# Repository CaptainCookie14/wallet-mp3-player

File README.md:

# wallet-mp3-player
This project is a small, portable MP3 player, designed to be roughly the size of a credit card. This project is all about minimal power consumption, small PCB design, and ease of use for the player.

HOW TO USE IT Insert a micro SD card containing MP3 or WAV files into the device. Turn it on using the battery and play the songs using the buttons. It does not require a phone or computer to play songs. Users can play, pause, and skip songs, and also change the volume using the buttons.

Features

Plays MP3 audio files Ultra-compact PCB design (credit card sized) Button-based controls (play/pause, next, previous, volume) Supports microSD storage for music files Low power consumption for portable devices Optional output for headphones or small speakers

HOW IT WORKS:

It is composed of a microcontroller, which reads the audio files from a storage module, usually a microSD card. The microcontroller then sends the decoded audio to an amplifier for output.

The buttons are always being read by the microcontroller, which controls the state of the player, the songs being played, and the volume.

HARDWARE USED:

-Microcontroller ( STM32F411CEU6x )
- Micro SD card module
- Audio DAC module
- Small audio amplifier
- Tactile and low-profile buttons
- Lithium battery and charging circuit
- PCB designed in KiCad

WIRING/CONNECTIONS:

- Micro SD card module is connected through SPI
- Audio module is connected through I2S or analog pins
- Buttons are connected to digital GPIOs with pull-ups
- Battery is connected through power management circuit

The goal of this project is to create a fully functional, pocket-sized music player that is:

- as thin as possible (under 5mm)
- at least 5 hours of playing time
- able to fit in your wallet
- cheap as possible to make (under 80$ per unit after considering battery, case, shipping & PCB assembly)

The PCB files in this repository were prepared using the JLCPCB KiCad plugin to streamline manufacturing and assembly.

After completing the schematic and PCB layout in KiCad, the plugin was used to:

Generate production-ready Gerber files
Export drill files (Excellon format)
Create a complete BOM (Bill of Materials) with part numbers
Generate a CPL (Pick and Place file) for SMT assembly
Automatically align component footprints with JLCPCB’s supported parts library

i also added the project files and schematic files used for kiCad

Status

Currently in development / testing stage. PCB revisions and firmware improvements are ongoing and am trying to get my first prototype tested.

BOM MATERIALS LIST:
| Ref                                   | Qty | Value             | Footprint       | LCSC Link                                                                                                                                                                                                                            |
| ------------------------------------- | --- | ----------------- | --------------- | ------------------------------------------------------------------------------------------------------------------------------------------------------------------------------------------------------------------------------------ |
| Y1                                    | 1   | 16 MHz crystal    | 3225            | [https://www.lcsc.com/product-detail/Crystals_YXC-Crystal-CX3225SB16000D0FLJCC_C13738.html](https://www.lcsc.com/product-detail/Crystals_YXC-Crystal-CX3225SB16000D0FLJCC_C13738.html)                                               |
| U5                                    | 1   | TPA6132A2RTE      | WQFN-16         | [https://www.lcsc.com/product-detail/Audio-ICs_Texas-Instruments-TPA6132A2RTE_C2863070.html](https://www.lcsc.com/product-detail/Audio-ICs_Texas-Instruments-TPA6132A2RTE_C2863070.html)                                             |
| U4                                    | 1   | PCM5102A          | TSSOP-20        | [https://www.lcsc.com/product-detail/Audio-ICs_Texas-Instruments-PCM5102A_C1520792.html](https://www.lcsc.com/product-detail/Audio-ICs_Texas-Instruments-PCM5102A_C1520792.html)                                                     |
| U3                                    | 1   | USBLC6-2SC6       | SOT-23-6        | [https://www.lcsc.com/product-detail/TVS-Diodes_STMicroelectronics-USBLC6-2SC6_C7519.html](https://www.lcsc.com/product-detail/TVS-Diodes_STMicroelectronics-USBLC6-2SC6_C7519.html)                                                 |
| U2                                    | 1   | AMS1117           | SOT-223         | [https://www.lcsc.com/product-detail/Linear-Voltage-Regulators_Advanced-Monolithic-Systems-AMS1117-3-3_C6186.html](https://www.lcsc.com/product-detail/Linear-Voltage-Regulators_Advanced-Monolithic-Systems-AMS1117-3-3_C6186.html) |
| U1                                    | 1   | STM32F411CEUx     | QFN-48          | [https://www.lcsc.com/product-detail/Microcontrollers-MCU-ST-Microelectronics-STM32F411CEUx_C60420.html](https://www.lcsc.com/product-detail/Microcontrollers-MCU-ST-Microelectronics-STM32F411CEUx_C60420.html)                     |
| SW2–SW6                               | 5   | Tactile switch    | SMD push button | [https://www.lcsc.com/product-detail/Tactile-Switches_XKB-TS-1187A_C318884.html](https://www.lcsc.com/product-detail/Tactile-Switches_XKB-TS-1187A_C318884.html)                                                                     |
| SW1                                   | 1   | SPDT switch       | PCM12           | [https://www.lcsc.com/product-detail/Slide-Switches_CW-PCM12_C109335.html](https://www.lcsc.com/product-detail/Slide-Switches_CW-PCM12_C109335.html)                                                                                 |
| R15,R16                               | 2   | 5.1kΩ             | 0402            | [https://www.lcsc.com/product-detail/Chip-Resistor-Surface-Mount_YAGEO-RC0402FR-075K1L_C25905.html](https://www.lcsc.com/product-detail/Chip-Resistor-Surface-Mount_YAGEO-RC0402FR-075K1L_C25905.html)                               |
| R13,R14                               | 2   | 10Ω               | 0402            | [https://www.lcsc.com/product-detail/Chip-Resistor-Surface-Mount_YAGEO-RC0402FR-0710RL_C25077.html](https://www.lcsc.com/product-detail/Chip-Resistor-Surface-Mount_YAGEO-RC0402FR-0710RL_C25077.html)                               |
| R11,R12                               | 2   | 450Ω              | 0402            | [https://www.lcsc.com/product-detail/Chip-Resistor-Surface-Mount_YAGEO-RC0402FR-07450RL_C25117.html](https://www.lcsc.com/product-detail/Chip-Resistor-Surface-Mount_YAGEO-RC0402FR-07450RL_C25117.html)                             |
| R2,R3                                 | 2   | 1.5kΩ             | 0402            | [https://www.lcsc.com/product-detail/Chip-Resistor-Surface-Mount_YAGEO-RC0402FR-071K5L_C25867.html](https://www.lcsc.com/product-detail/Chip-Resistor-Surface-Mount_YAGEO-RC0402FR-071K5L_C25867.html)                               |
| R1,R4–R7,R9,R10                       | 7   | 10kΩ              | 0402            | [https://www.lcsc.com/product-detail/Chip-Resistor-Surface-Mount_YAGEO-RC0402FR-0710KL_C25744.html](https://www.lcsc.com/product-detail/Chip-Resistor-Surface-Mount_YAGEO-RC0402FR-0710KL_C25744.html)                               |
| J5                                    | 1   | 3.5mm audio jack  | SMT             | [https://www.lcsc.com/product-detail/Audio-Connectors_CUI-Devices-SJ-3523-SMT_C4991872.html](https://www.lcsc.com/product-detail/Audio-Connectors_CUI-Devices-SJ-3523-SMT_C4991872.html)                                             |
| J4                                    | 1   | USB-C receptacle  | 16P USB2.0      | [https://www.lcsc.com/product-detail/USB-Connectors_XKB-Connectivity-U262-16XN-4BVC11_C2894897.html](https://www.lcsc.com/product-detail/USB-Connectors_XKB-Connectivity-U262-16XN-4BVC11_C2894897.html)                             |
| J2                                    | 1   | Micro SD socket   | TF-01A          | [https://www.lcsc.com/product-detail/Memory-Card-Sockets_Jinling-Group-TF-01A_C91145.html](https://www.lcsc.com/product-detail/Memory-Card-Sockets_Jinling-Group-TF-01A_C91145.html)                                                 |
| J1                                    | 1   | 4-pin header      | 2.54mm          | [https://www.lcsc.com/product-detail/Pin-Header-Sockets_Generic-2-54mm-pin-header_CNA.html](https://www.lcsc.com/product-detail/Pin-Header-Sockets_Generic-2-54mm-pin-header_CNA.html)                                               |
| FB1                                   | 1   | 120Ω ferrite bead | 0603            | [https://www.lcsc.com/product-detail/Ferrite-Beads_Murata-BLM18AG121SN1D_C76892.html](https://www.lcsc.com/product-detail/Ferrite-Beads_Murata-BLM18AG121SN1D_C76892.html)                                                           |
| D1,D2                                 | 2   | LED               | 0805            | [https://www.lcsc.com/product-detail/LED-Indication_YONGYUTAI-0805-LED_C2290.html](https://www.lcsc.com/product-detail/LED-Indication_YONGYUTAI-0805-LED_C2290.html)                                                                 |
| C44,C45                               | 2   | 2.2nF             | 0402            | [https://www.lcsc.com/product-detail/Ceramic-Capacitors_YAGEO-CC0402KRX7R7BB222_C1531.html](https://www.lcsc.com/product-detail/Ceramic-Capacitors_YAGEO-CC0402KRX7R7BB222_C1531.html)                                               |
| C23,C26,C27,C43                       | 4   | 2.2µF             | 0402            | [https://www.lcsc.com/product-detail/Ceramic-Capacitors_YAGEO-CC0402MRX5R5BB225_C12530.html](https://www.lcsc.com/product-detail/Ceramic-Capacitors_YAGEO-CC0402MRX5R5BB225_C12530.html)                                             |
| C10,C11                               | 2   | 22µF              | 0805            | [https://www.lcsc.com/product-detail/Ceramic-Capacitors_Murata-GRM21BR61A226ME44_C45783.html](https://www.lcsc.com/product-detail/Ceramic-Capacitors_Murata-GRM21BR61A226ME44_C45783.html)                                           |
| C8,C9                                 | 2   | 10pF              | 0402            | [https://www.lcsc.com/product-detail/Ceramic-Capacitors_YAGEO-CC0402JRNPO9BN100_C32949.html](https://www.lcsc.com/product-detail/Ceramic-Capacitors_YAGEO-CC0402JRNPO9BN100_C32949.html)                                             |
| C6,C7,C24,C25,C30,C31                 | 6   | 1µF               | 0402            | [https://www.lcsc.com/product-detail/Ceramic-Capacitors_YAGEO-CC0402MRX5R5BB105_C52923.html](https://www.lcsc.com/product-detail/Ceramic-Capacitors_YAGEO-CC0402MRX5R5BB105_C52923.html)                                             |
| C5                                    | 1   | 10nF              | 0402            | [https://www.lcsc.com/product-detail/Ceramic-Capacitors_YAGEO-CC0402KRX7R9BB103_C15195.html](https://www.lcsc.com/product-detail/Ceramic-Capacitors_YAGEO-CC0402KRX7R9BB103_C15195.html)                                             |
| C4,C15,C17,C19,C32                    | 5   | 10µF              | 0805            | [https://www.lcsc.com/product-detail/Ceramic-Capacitors_Murata-GRM21BR61A106KE19_C15850.html](https://www.lcsc.com/product-detail/Ceramic-Capacitors_Murata-GRM21BR61A106KE19_C15850.html)                                           |
| C1–C3,C12–C14,C16,C18,C22,C28–C29,C33 | 12  | 100nF             | 0402            | [https://www.lcsc.com/product-detail/Ceramic-Capacitors_YAGEO-CC0402KRX7R7BB104_C1525.html](https://www.lcsc.com/product-detail/Ceramic-Capacitors_YAGEO-CC0402KRX7R7BB104_C1525.html)                                               |

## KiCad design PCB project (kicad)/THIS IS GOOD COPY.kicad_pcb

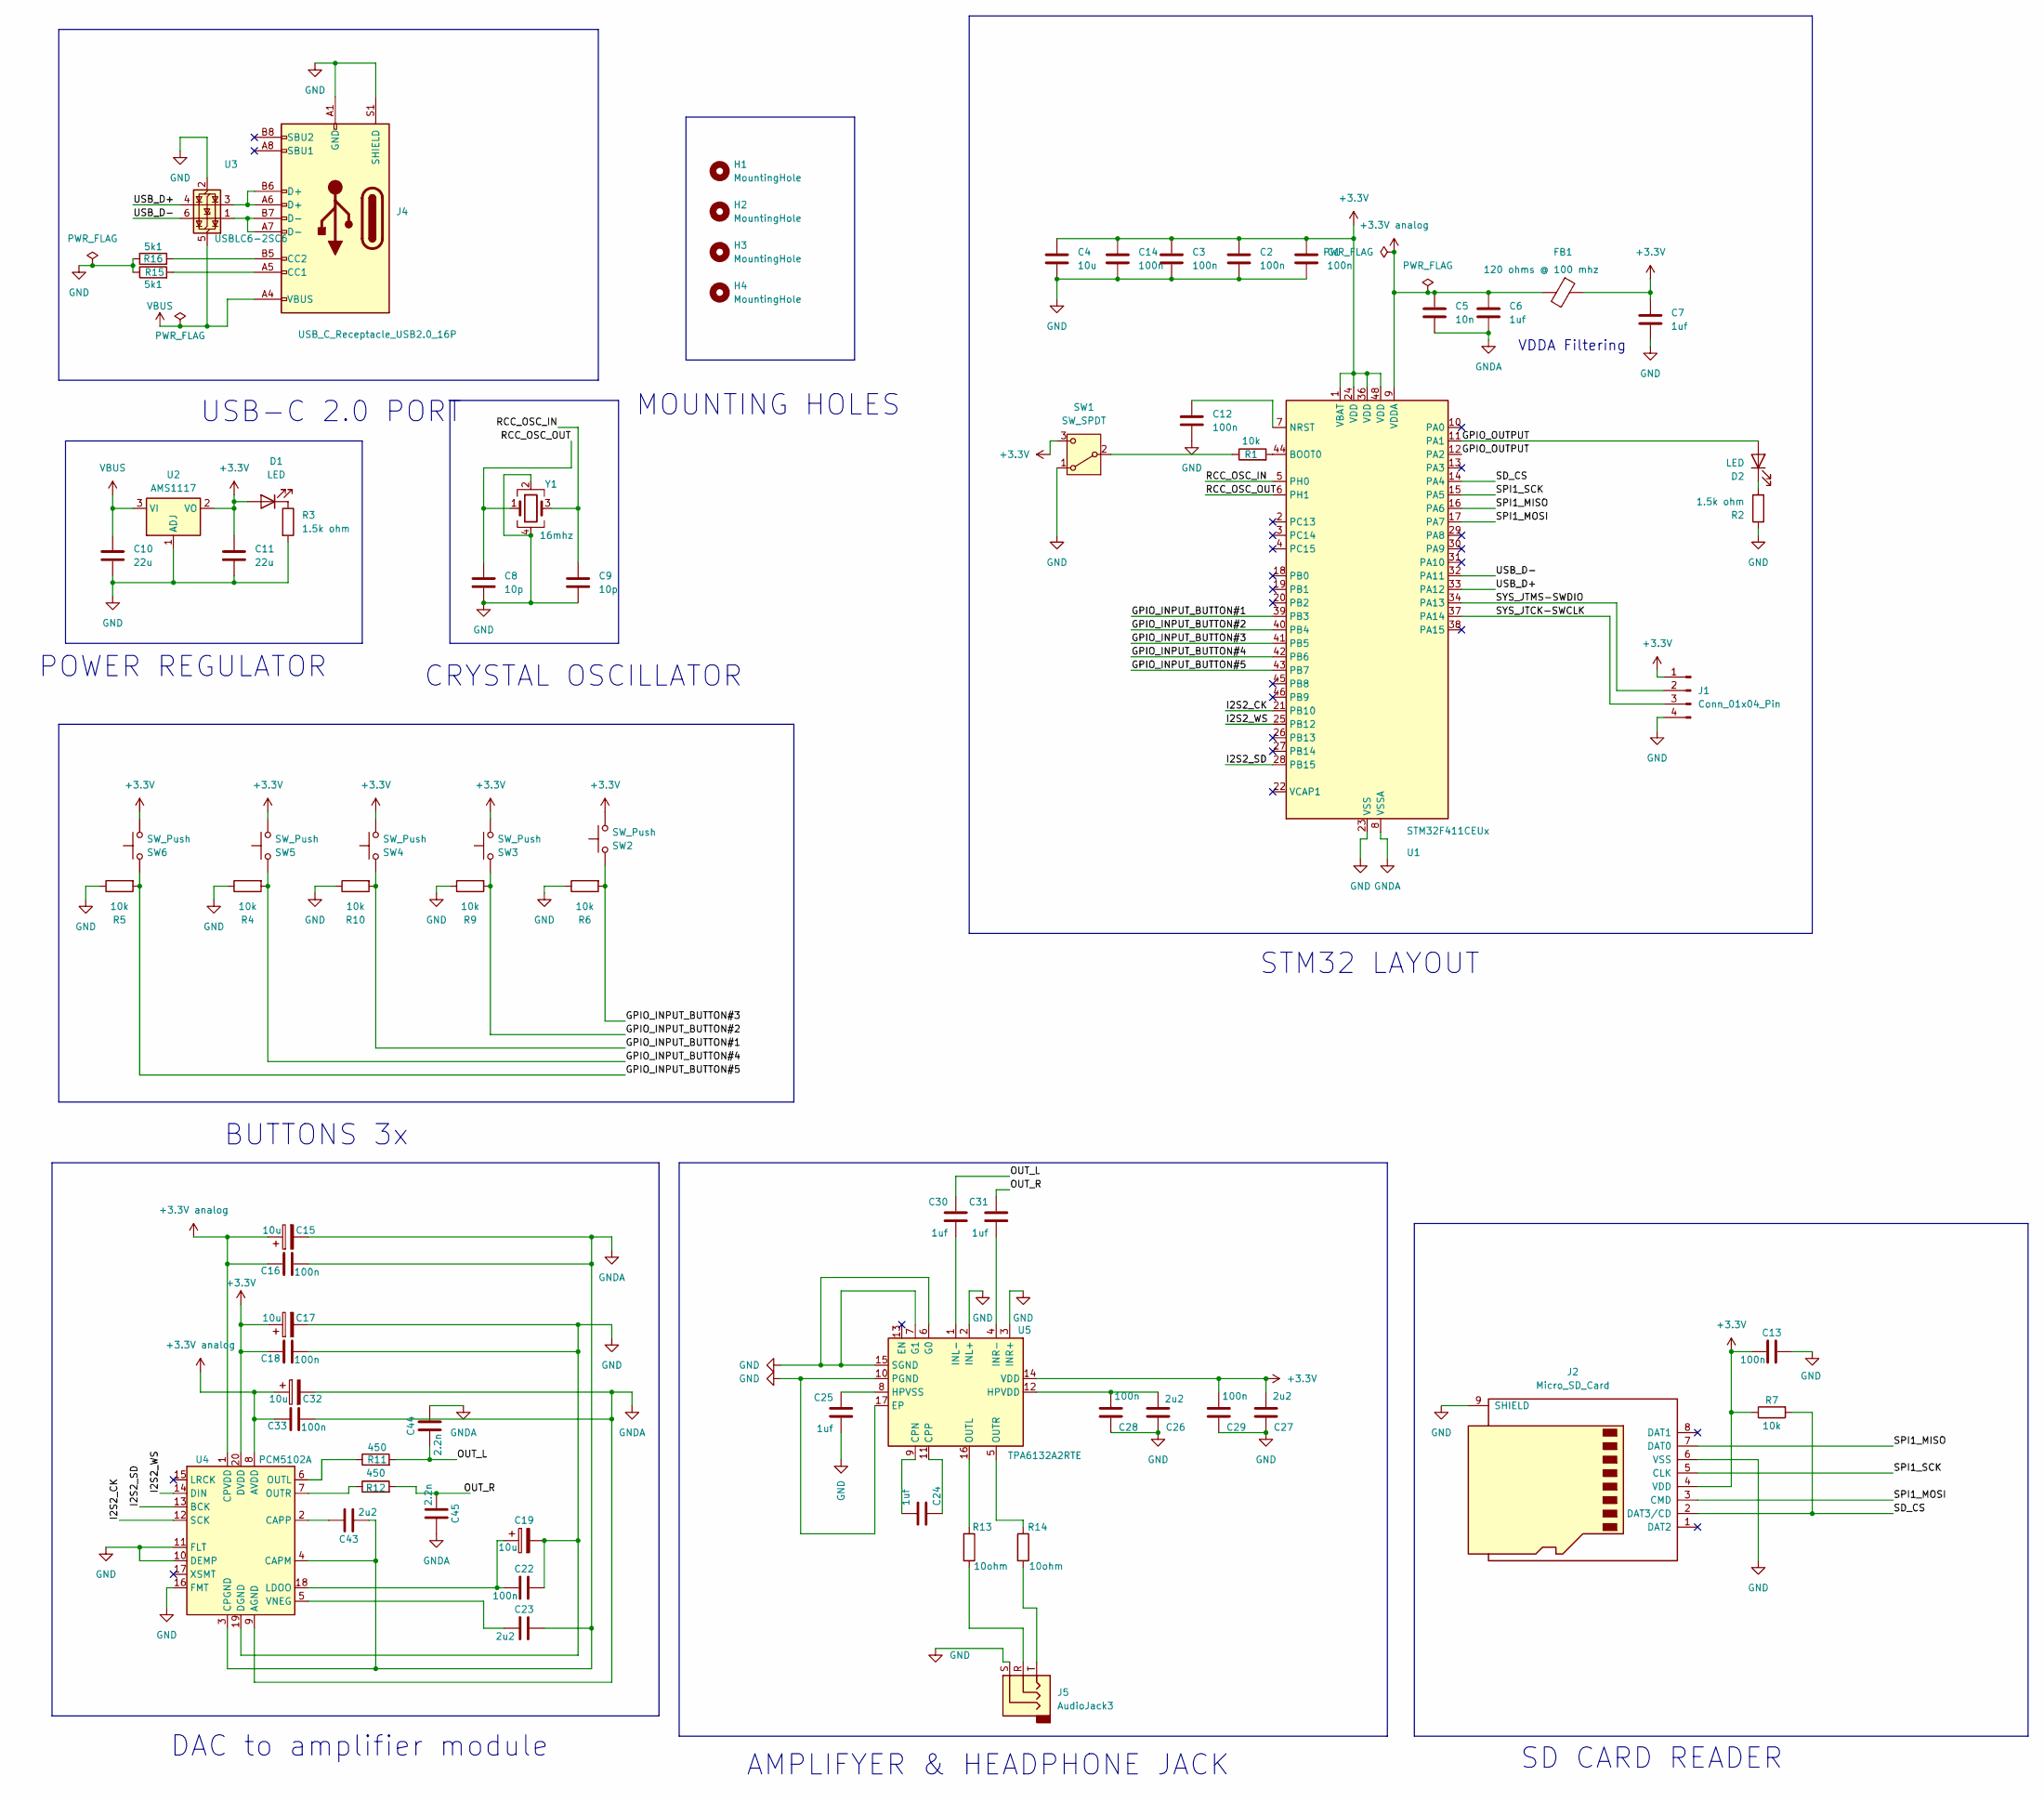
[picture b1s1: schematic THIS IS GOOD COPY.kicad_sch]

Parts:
C1, C2, C3, C12, C13, C14, C16, C18, C22, C28, C29, C33: 100n; C_0402_1005Metric
C4, C15, C17, C19, C32: 10u; C_0805_2012Metric
C5: 10n; C_0402_1005Metric
C6, C7, C24, C25, C30, C31: 1uf; C_0402_1005Metric
C8, C9: 10p; C_0402_1005Metric
C10, C11: 22u; C_0805_2012Metric
C23, C26, C27, C43: 2u2; C_0402_1005Metric
C44, C45: 2.2n; C_0402_1005Metric
D1, D2: LED; LED_0805_2012Metric
FB1: 120 ohms @ 100 mhz; L_0603_1608Metric
H1, H2, H3, H4: MountingHole; MountingHole_2.2mm_M2
J1: Conn_01x04_Pin; PinHeader_1x04_P2.54mm_Vertical
J2: Micro_SD_Card; TF-01A
J4: USB_C_Receptacle_USB2.0_16P; USB_C_Receptacle_HCTL_HC-TYPE-C-16P-01A
J5: AudioJack3; Jack_3.5mm_CUI_SJ-3523-SMT_Horizontal
R1, R4, R5, R6, R7, R9, R10: 10k; R_0402_1005Metric
R2, R3: 1.5k ohm; R_0402_1005Metric
R11, R12: 450; R_0402_1005Metric
R13, R14: 10ohm; R_0402_1005Metric
R15, R16: 5k1; R_0402_1005Metric
SW1: SW_SPDT; SW_SPDT_PCM12
SW2, SW3, SW4, SW5, SW6: SW_Push; SW_Push_1P1T_XKB_TS-1187A
U1: STM32F411CEUx; QFN-48-1EP_7x7mm_P0.5mm_EP5.6x5.6mm
U2: AMS1117; SOT-223-3_TabPin2
U3: USBLC6-2SC6; SOT-23-6
U4: PCM5102A; TSSOP-20_4.4x6.5mm_P0.65mm
U5: TPA6132A2RTE; WQFN-16-1EP_3x3mm_P0.5mm_EP1.6x1.6mm_ThermalVias
Y1: 16mhz; Crystal_SMD_3225-4Pin_3.2x2.5mm

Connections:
+3.3V: C1.1, C2.1, C3.1, C4.1, C7.1, C11.1, C13.2, C14.1, C17.1, C18.1, C27.2, C29.2, D1.2 (A), FB1.1, J1.1, J2.4 (VDD), R7.1, SW1.3 (C), SW2.1, SW3.1, SW4.1, SW5.1, SW6.1, U1.1 (VBAT), U1.24 (VDD), U1.36 (VDD), U1.48 (VDD), U2.2 (VO), U4.20 (DVDD), U5.14 (VDD)
+3.3V analog: C5.1, C6.1, C15.1, C16.1, C32.1, C33.1, FB1.2, U1.9 (VDDA), U4.1 (CPVDD), U4.8 (AVDD)
/GPIO_INPUT_BUTTON#1: R10.2, SW4.2, U1.39 (PB3)
/GPIO_INPUT_BUTTON#2: R9.2, SW3.2, U1.40 (PB4)
/GPIO_INPUT_BUTTON#3: R6.2, SW2.2, U1.41 (PB5)
/GPIO_INPUT_BUTTON#4: R4.2, SW5.2, U1.42 (PB6)
/GPIO_INPUT_BUTTON#5: R5.2, SW6.2, U1.43 (PB7)
/GPIO_OUTPUT: D2.2 (A), U1.11 (PA1), U1.12 (PA2)
/I2S2_CK: U1.21 (PB10), U4.12 (SCK)
/I2S2_SD: U1.28 (PB15), U4.13 (BCK)
/I2S2_WS: U1.25 (PB12), U4.14 (DIN)
/OUT_L: C30.1, C44.2, R11.2
/OUT_R: C31.1, C45.2, R12.2
/RCC_OSC_IN: C9.1, U1.5 (PH0), Y1.3
/RCC_OSC_OUT: C8.1, U1.6 (PH1), Y1.1
/SD_CS: J2.2 (DAT3/CD), R7.2, U1.14 (PA4)
/SPI1_MISO: J2.7 (DAT0), U1.16 (PA6)
/SPI1_MOSI: J2.3 (CMD), U1.17 (PA7)
/SPI1_SCK: J2.5 (CLK), U1.15 (PA5)
/SYS_JTCK-SWCLK: J1.3, U1.37 (PA14)
/SYS_JTMS-SWDIO: J1.2, U1.34 (PA13)
/USB_D+: U1.33 (PA12), U3.4 (I/O2)
/USB_D-: U1.32 (PA11), U3.6 (I/O1)
GND: C1.2, C2.2, C3.2, C4.2, C7.2, C8.2, C9.2, C10.2, C11.2, C12.2, C13.1, C14.2, C17.2, C18.2, C19.2, C22.1, C25.2, C26.1, C27.1, C28.1, C29.1, J1.4, J2.6 (VSS), J2.9 (SHIELD), J4.A1 (GND), J4.A12 (GND), J4.B1 (GND), J4.B12 (GND), J4.S1 (SHIELD), J5.S, R2.1, R3.2, R4.1, R5.1, R6.1, R9.1, R10.1, R15.1, R16.1, SW1.1 (A), U1.23 (VSS), U1.35 (VSS), U1.47 (VSS), U1.49 (VSS), U2.1 (ADJ), U3.2 (GND), U4.10 (DEMP), U4.11 (FLT), U4.16 (FMT), U4.19 (DGND), U5.2 (INL+), U5.3 (INR+), U5.6 (G0), U5.7 (G1), U5.10 (PGND), U5.15 (SGND), U5.17 (EP), Y1.2, Y1.4
GNDA: C5.2, C6.2, C15.2, C16.2, C23.1, C32.2, C33.2, C43.2, C44.1, C45.1, U1.8 (VSSA), U4.3 (CPGND), U4.4 (CAPM), U4.9 (AGND)
unnamed: D1.1 (K), R3.1
unnamed: D2.1 (K), R2.2
unnamed: J4.A5 (CC1), R16.2
unnamed: J4.B5 (CC2), R15.2
unnamed: J4.A6 (D+), J4.B6 (D+), U3.3 (I/O2)
unnamed: J4.A7 (D-), J4.B7 (D-), U3.1 (I/O1)
unnamed: J5.R, R13.2
unnamed: J5.T, R14.2
unnamed: R1.1, SW1.2 (B)
unnamed: R1.2, U1.44 (BOOT0)
unnamed: C12.1, U1.7 (NRST)
unnamed: C43.1, U4.2 (CAPP)
unnamed: C19.1, C22.2, U4.18 (LDOO)
unnamed: R11.1, U4.6 (OUTL)
unnamed: R12.1, U4.7 (OUTR)
unnamed: C23.2, U4.5 (VNEG)
unnamed: C24.2, U5.9 (CPN)
unnamed: C24.1, U5.11 (CPP)
unnamed: C26.2, C28.2, U5.12 (HPVDD)
unnamed: C25.1, U5.8 (HPVSS)
unnamed: C30.2, U5.1 (INL-)
unnamed: C31.2, U5.4 (INR-)
unnamed: R13.1, U5.16 (OUTL)
unnamed: R14.1, U5.5 (OUTR)
VBUS: C10.1, J4.A4 (VBUS), J4.A9 (VBUS), J4.B4 (VBUS), J4.B9 (VBUS), U2.3 (VI), U3.5 (VBUS)

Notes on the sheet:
DAC to amplifier module
CRYSTAL OSCILLATOR
AMPLIFYER & HEADPHONE JACK
POWER REGULATOR
VDDA Filtering
SD CARD READER
MOUNTING HOLES
BUTTONS 3x
USB-C 2.0 PORT
STM32 LAYOUT

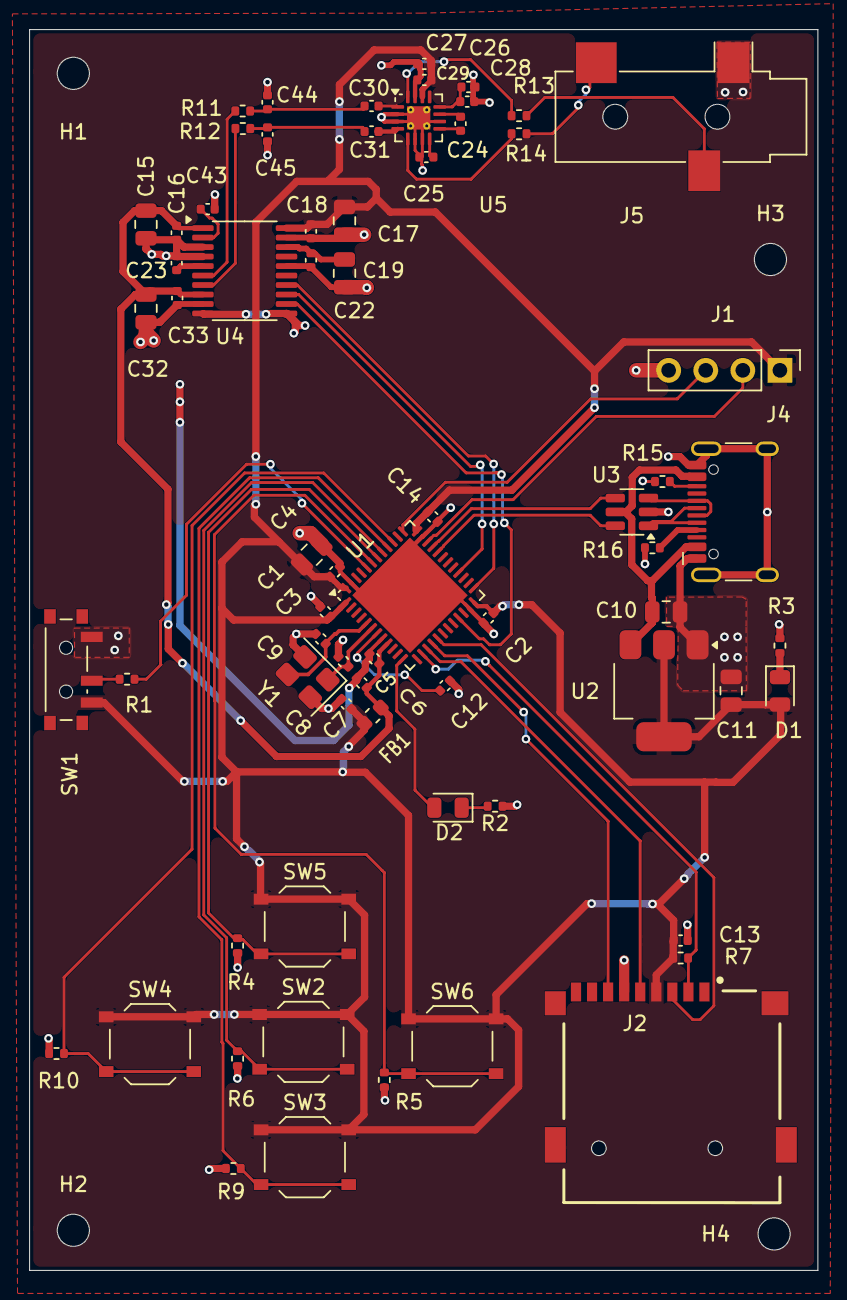
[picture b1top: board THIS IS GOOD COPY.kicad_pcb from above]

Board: 2 copper layers, 54.0 x 85.0 mm, 72 parts (0 on the bottom side), 50 nets.

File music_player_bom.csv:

Designator,Footprint,Quantity,Value,LCSC Part #
"C1, C12, C13, C14, C16, C18, C2, C22, C28, C29, C3, C33",0402,12,100n,
"C10, C11",0805,2,22u,
"C15, C17, C19, C32, C4",0805,5,10u,
"C23, C26, C27, C43",0402,4,2u2,
"C24, C25, C30, C31, C6, C7",0402,6,1uf,
"C44, C45",0402,2,2.2n,
C5,0402,1,10n,
"C8, C9",0402,2,10p,
"D1, D2",0805,2,LED,
FB1,0603,1,120 ohms @ 100 mhz,
J1,PinHeader_1x04_P2.54mm_Vertical,1,Conn_01x04_Pin,
J2,TF-01A,1,Micro_SD_Card,
J4,USB_C_Receptacle_HCTL_HC-TYPE-C-16P-01A,1,USB_C_Receptacle_USB2.0_16P,
J5,Jack_3.5mm_CUI_SJ-3523-SMT_Horizontal,1,AudioJack3,
"R1, R10, R4, R5, R6, R7, R9",0402,7,10k,
"R11, R12",0402,2,450,
"R13, R14",0402,2,10ohm,
"R15, R16",0402,2,5k1,
"R2, R3",0402,2,1.5k ohm,
SW1,SW_SPDT_PCM12,1,SW_SPDT,
"SW2, SW3, SW4, SW5, SW6",SW_Push_1P1T_XKB_TS-1187A,5,SW_Push,
U1,QFN-48-1EP_7x7mm_P0.5mm_EP5.6x5.6mm,1,STM32F411CEUx,
U2,SOT-223-3_TabPin2,1,AMS1117,
U3,SOT-23-6,1,USBLC6-2SC6,
U4,TSSOP-20_4.4x6.5mm_P0.65mm,1,PCM5102A,
U5,WQFN-16-1EP_3x3mm_P0.5mm_EP1.6x1.6mm_ThermalVias,1,TPA6132A2RTE,
Y1,Crystal_SMD_3225-4Pin_3.2x2.5mm,1,16mhz,

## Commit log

2026-03-28 Add files via upload
    these files are configured for JLC PCB
2026-03-29 Create placeholder
2026-03-29 Create jlcpcbfiles
2026-03-29 Create photos
2026-03-29 Create firmware
2026-03-29 Implement WAV playback functionality in firmware
2026-03-29 Add BOM materials list to README
    Added a BOM materials list with component details.
2026-03-29 Revise BOM materials list and add LCSC links
    Updated BOM materials list with improved formatting and added LCSC links for components.
2026-03-29 Add usage instructions to README
    Added usage instructions for the MP3 player.
2026-03-29 Create BOM
2026-03-29 Update README with images and feature details
    Added images and enhanced features section in README.
2026-03-29 Improve README clarity and instructions
    Reworded project description and usage instructions for clarity.
2026-03-29 Revise README for improved clarity and formatting
    Updated features, hardware used, and wiring sections for clarity and consistency.
